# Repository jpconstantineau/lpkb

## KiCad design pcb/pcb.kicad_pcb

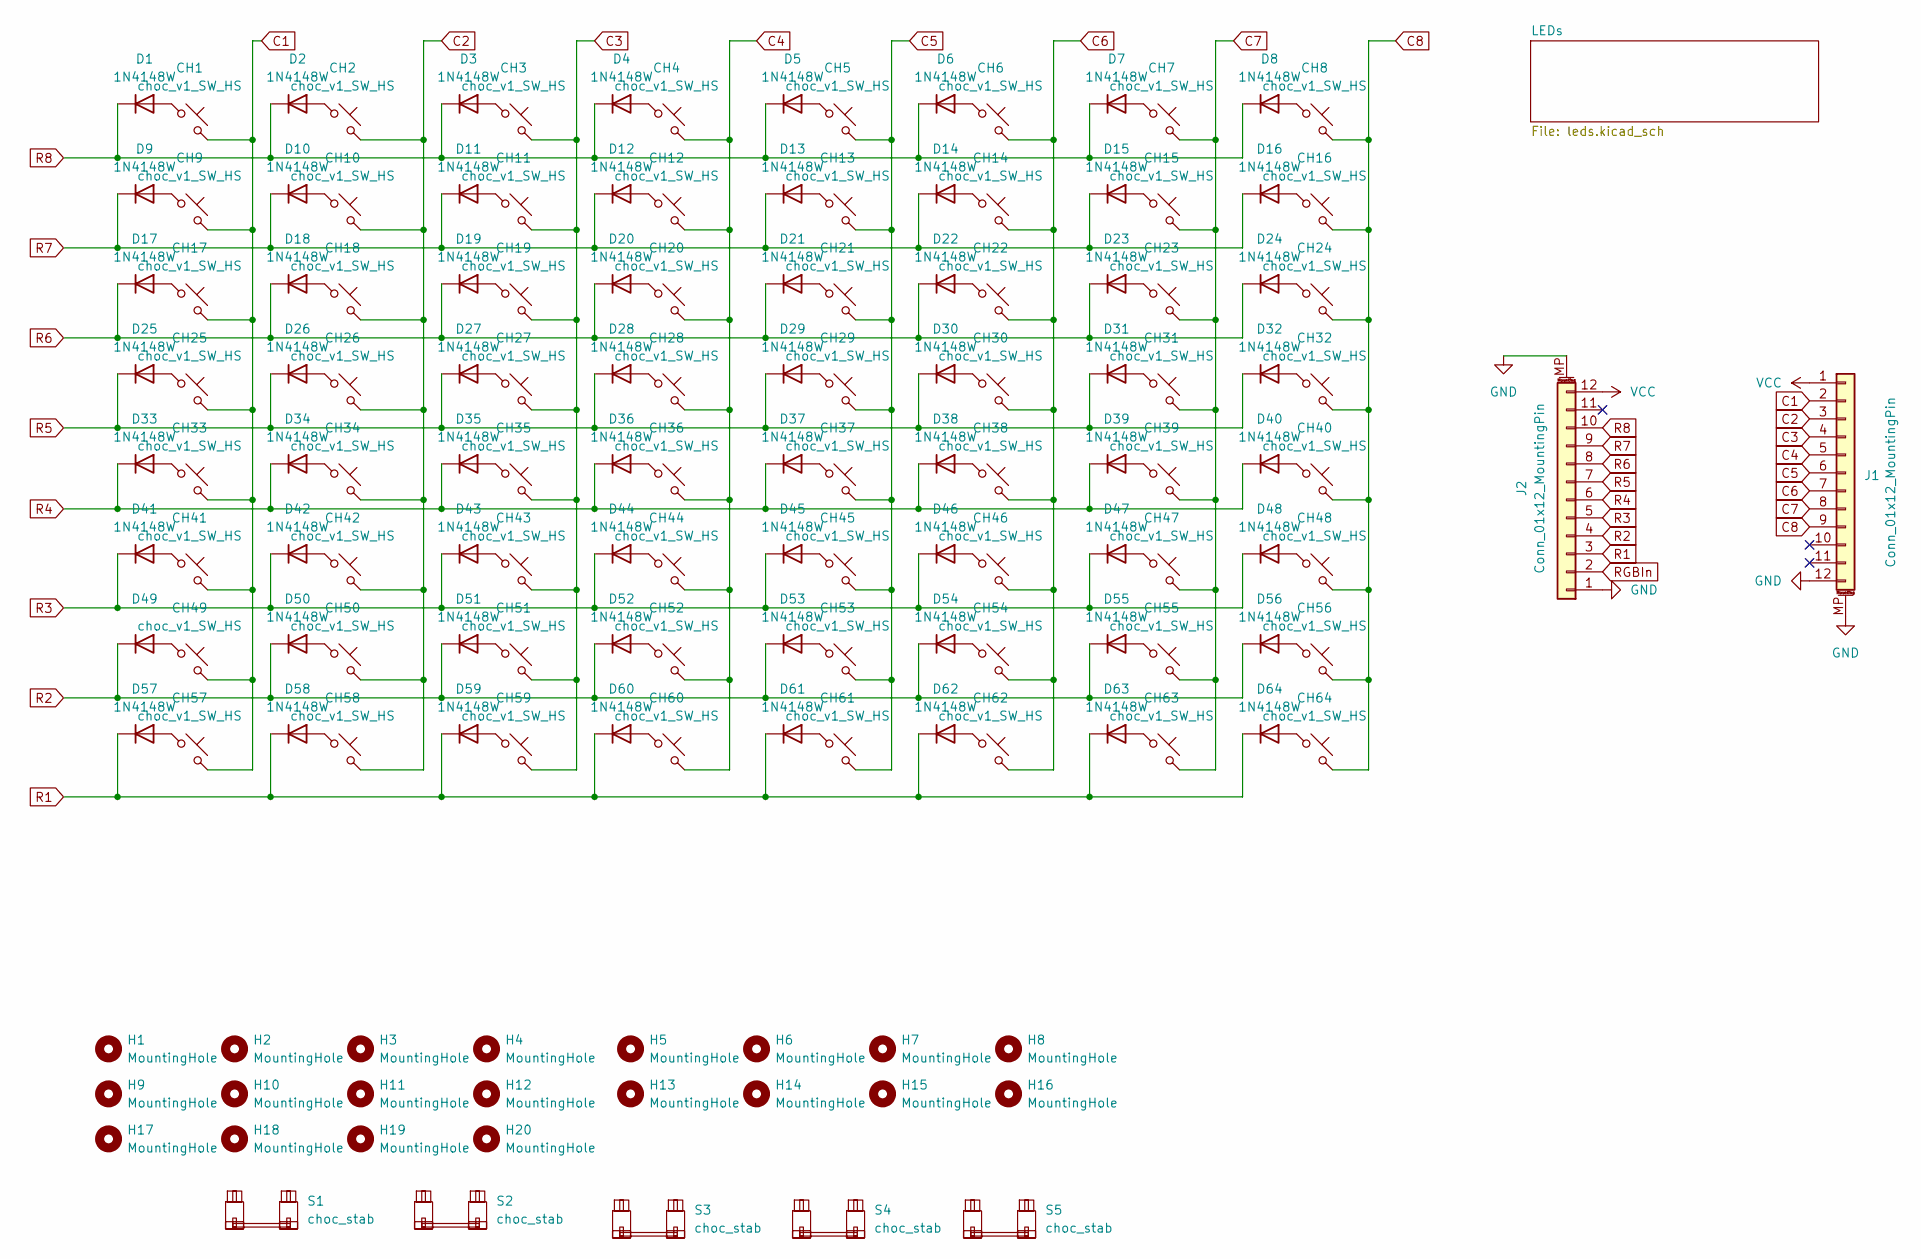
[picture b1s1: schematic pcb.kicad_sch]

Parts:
CH1, CH2, CH3, CH4, CH5, CH6, CH7, CH8, CH9, CH10, CH11, CH12, CH13, CH14, CH15, CH16, CH17, CH18, CH19, CH20, CH21, CH22, CH23, CH24, CH25, CH26, CH27, CH28, CH29, CH30, CH31, CH32, CH33, CH34, CH35, CH36, CH37, CH38, CH39, CH40, CH41, CH42, CH43, CH44, CH45, CH46, CH47, CH48, CH49, CH50, CH51, CH52, CH53, CH54, CH55, CH56, CH57, CH58, CH59, CH60, CH61, CH62, CH63, CH64: choc_v1_SW_HS; SW_choc_v1_HS_CPG135001S30_1u
D1, D2, D3, D4, D5, D6, D7, D8, D9, D10, D11, D12, D13, D14, D15, D16, D17, D18, D19, D20, D21, D22, D23, D24, D25, D26, D27, D28, D29, D30, D31, D32, D33, D34, D35, D36, D37, D38, D39, D40, D41, D42, D43, D44, D45, D46, D47, D48, D49, D50, D51, D52, D53, D54, D55, D56, D57, D58, D59, D60, D61, D62, D63, D64: 1N4148W; D_SOD-123
H1, H2, H3, H4, H5, H6, H7, H8, H9, H10, H11, H12, H13, H14, H15, H16, H17, H18, H19, H20: MountingHole; MountingHole_2.2mm_M2_ISO14580
J1, J2: Conn_01x12_MountingPin; JUSHUO-AFC07-S12FCC-00_C11051_1x12-1MP_P0.50mm_Horizontal
S1, S2, S3, S4, S5: choc_stab; STAB_choc_2u

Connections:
C1: CH1.2, CH9.2, CH17.2, CH25.2, CH33.2, CH41.2, CH49.2, CH57.2, J1.2
C2: CH2.2, CH10.2, CH18.2, CH26.2, CH34.2, CH42.2, CH50.2, CH58.2, J1.3
C3: CH3.2, CH11.2, CH19.2, CH27.2, CH35.2, CH43.2, CH51.2, CH59.2, J1.4
C4: CH4.2, CH12.2, CH20.2, CH28.2, CH36.2, CH44.2, CH52.2, CH60.2, J1.5
C5: CH5.2, CH13.2, CH21.2, CH29.2, CH37.2, CH45.2, CH53.2, CH61.2, J1.6
C6: CH6.2, CH14.2, CH22.2, CH30.2, CH38.2, CH46.2, CH54.2, CH62.2, J1.7
C7: CH7.2, CH15.2, CH23.2, CH31.2, CH39.2, CH47.2, CH55.2, CH63.2, J1.8
C8: CH8.2, CH16.2, CH24.2, CH32.2, CH40.2, CH48.2, CH56.2, CH64.2, J1.9
GND: J1.12, J1.MP (MountPin), J2.1, J2.MP (MountPin); also elsewhere on the board
unnamed: CH1.1, D1.2 (A)
unnamed: CH2.1, D2.2 (A)
unnamed: CH3.1, D3.2 (A)
unnamed: CH4.1, D4.2 (A)
unnamed: CH5.1, D5.2 (A)
unnamed: CH6.1, D6.2 (A)
unnamed: CH7.1, D7.2 (A)
unnamed: CH8.1, D8.2 (A)
unnamed: CH9.1, D9.2 (A)
unnamed: CH10.1, D10.2 (A)
unnamed: CH11.1, D11.2 (A)
unnamed: CH12.1, D12.2 (A)
unnamed: CH13.1, D13.2 (A)
unnamed: CH14.1, D14.2 (A)
unnamed: CH15.1, D15.2 (A)
unnamed: CH16.1, D16.2 (A)
unnamed: CH17.1, D17.2 (A)
unnamed: CH18.1, D18.2 (A)
unnamed: CH19.1, D19.2 (A)
unnamed: CH20.1, D20.2 (A)
unnamed: CH21.1, D21.2 (A)
unnamed: CH22.1, D22.2 (A)
unnamed: CH23.1, D23.2 (A)
unnamed: CH24.1, D24.2 (A)
unnamed: CH25.1, D25.2 (A)
unnamed: CH26.1, D26.2 (A)
unnamed: CH27.1, D27.2 (A)
unnamed: CH28.1, D28.2 (A)
unnamed: CH29.1, D29.2 (A)
unnamed: CH30.1, D30.2 (A)
unnamed: CH31.1, D31.2 (A)
unnamed: CH32.1, D32.2 (A)
unnamed: CH33.1, D33.2 (A)
unnamed: CH34.1, D34.2 (A)
unnamed: CH35.1, D35.2 (A)
unnamed: CH36.1, D36.2 (A)
unnamed: CH37.1, D37.2 (A)
unnamed: CH38.1, D38.2 (A)
unnamed: CH39.1, D39.2 (A)
unnamed: CH40.1, D40.2 (A)
unnamed: CH41.1, D41.2 (A)
unnamed: CH42.1, D42.2 (A)
unnamed: CH43.1, D43.2 (A)
unnamed: CH44.1, D44.2 (A)
unnamed: CH45.1, D45.2 (A)
unnamed: CH46.1, D46.2 (A)
unnamed: CH47.1, D47.2 (A)
unnamed: CH48.1, D48.2 (A)
unnamed: CH49.1, D49.2 (A)
unnamed: CH50.1, D50.2 (A)
unnamed: CH51.1, D51.2 (A)
unnamed: CH52.1, D52.2 (A)
unnamed: CH53.1, D53.2 (A)
unnamed: CH54.1, D54.2 (A)
unnamed: CH55.1, D55.2 (A)
unnamed: CH56.1, D56.2 (A)
unnamed: CH57.1, D57.2 (A)
unnamed: CH58.1, D58.2 (A)
unnamed: CH59.1, D59.2 (A)
unnamed: CH60.1, D60.2 (A)
unnamed: CH61.1, D61.2 (A)
unnamed: CH62.1, D62.2 (A)
unnamed: CH63.1, D63.2 (A)
unnamed: CH64.1, D64.2 (A)
R1: D57.1 (K), D58.1 (K), D59.1 (K), D60.1 (K), D61.1 (K), D62.1 (K), D63.1 (K), D64.1 (K), J2.3
R2: D49.1 (K), D50.1 (K), D51.1 (K), D52.1 (K), D53.1 (K), D54.1 (K), D55.1 (K), D56.1 (K), J2.4
R3: D41.1 (K), D42.1 (K), D43.1 (K), D44.1 (K), D45.1 (K), D46.1 (K), D47.1 (K), D48.1 (K), J2.5
R4: D33.1 (K), D34.1 (K), D35.1 (K), D36.1 (K), D37.1 (K), D38.1 (K), D39.1 (K), D40.1 (K), J2.6
R5: D25.1 (K), D26.1 (K), D27.1 (K), D28.1 (K), D29.1 (K), D30.1 (K), D31.1 (K), D32.1 (K), J2.7
R6: D17.1 (K), D18.1 (K), D19.1 (K), D20.1 (K), D21.1 (K), D22.1 (K), D23.1 (K), D24.1 (K), J2.8
R7: D9.1 (K), D10.1 (K), D11.1 (K), D12.1 (K), D13.1 (K), D14.1 (K), D15.1 (K), D16.1 (K), J2.9
R8: D1.1 (K), D2.1 (K), D3.1 (K), D4.1 (K), D5.1 (K), D6.1 (K), D7.1 (K), D8.1 (K), J2.10
RGBIn: J2.2; also elsewhere on the board
VCC: J1.1, J2.12; also elsewhere on the board

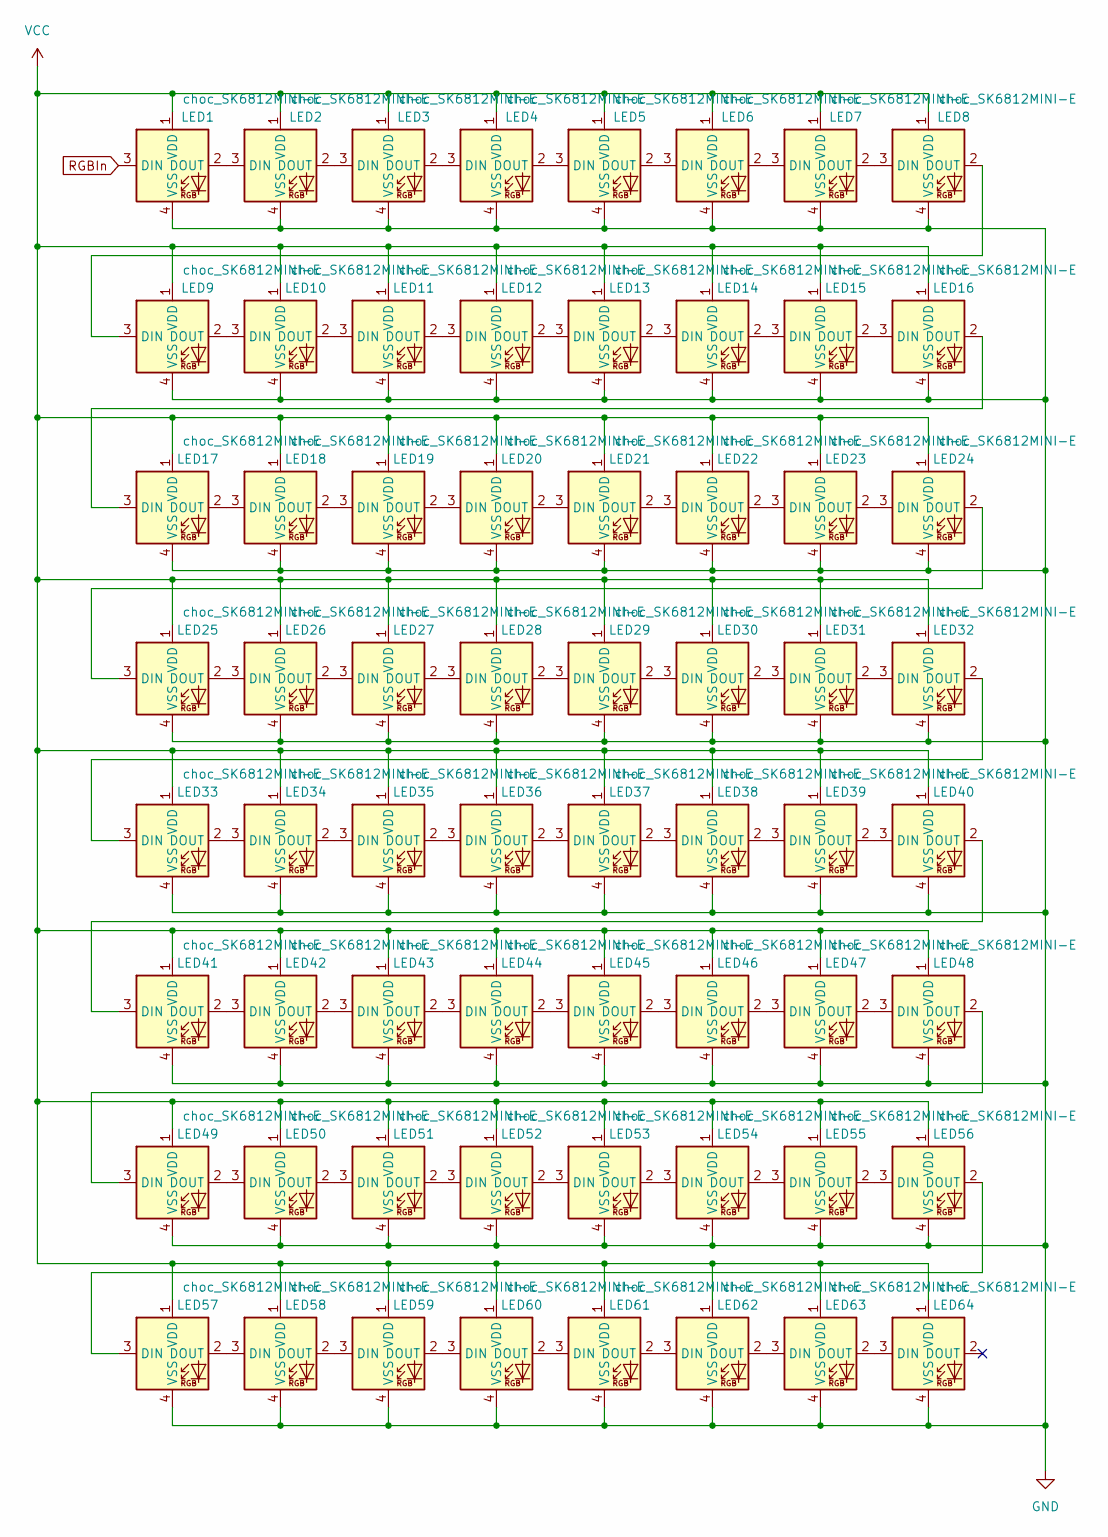
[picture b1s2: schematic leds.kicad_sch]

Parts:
LED1, LED2, LED3, LED4, LED5, LED6, LED7, LED8, LED9, LED10, LED11, LED12, LED13, LED14, LED15, LED16, LED17, LED18, LED19, LED20, LED21, LED22, LED23, LED24, LED25, LED26, LED27, LED28, LED29, LED30, LED31, LED32, LED33, LED34, LED35, LED36, LED37, LED38, LED39, LED40, LED41, LED42, LED43, LED44, LED45, LED46, LED47, LED48, LED49, LED50, LED51, LED52, LED53, LED54, LED55, LED56, LED57, LED58, LED59, LED60, LED61, LED62, LED63, LED64: choc_SK6812MINI-E; LED_choc_6028R

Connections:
GND: LED1.4 (VSS), LED2.4 (VSS), LED3.4 (VSS), LED4.4 (VSS), LED5.4 (VSS), LED6.4 (VSS), LED7.4 (VSS), LED8.4 (VSS), LED9.4 (VSS), LED10.4 (VSS), LED11.4 (VSS), LED12.4 (VSS), LED13.4 (VSS), LED14.4 (VSS), LED15.4 (VSS), LED16.4 (VSS), LED17.4 (VSS), LED18.4 (VSS), LED19.4 (VSS), LED20.4 (VSS), LED21.4 (VSS), LED22.4 (VSS), LED23.4 (VSS), LED24.4 (VSS), LED25.4 (VSS), LED26.4 (VSS), LED27.4 (VSS), LED28.4 (VSS), LED29.4 (VSS), LED30.4 (VSS), LED31.4 (VSS), LED32.4 (VSS), LED33.4 (VSS), LED34.4 (VSS), LED35.4 (VSS), LED36.4 (VSS), LED37.4 (VSS), LED38.4 (VSS), LED39.4 (VSS), LED40.4 (VSS), LED41.4 (VSS), LED42.4 (VSS), LED43.4 (VSS), LED44.4 (VSS), LED45.4 (VSS), LED46.4 (VSS), LED47.4 (VSS), LED48.4 (VSS), LED49.4 (VSS), LED50.4 (VSS), LED51.4 (VSS), LED52.4 (VSS), LED53.4 (VSS), LED54.4 (VSS), LED55.4 (VSS), LED56.4 (VSS), LED57.4 (VSS), LED58.4 (VSS), LED59.4 (VSS), LED60.4 (VSS), LED61.4 (VSS), LED62.4 (VSS), LED63.4 (VSS), LED64.4 (VSS); also elsewhere on the board
unnamed: LED1.2 (DOUT), LED2.3 (DIN)
unnamed: LED2.2 (DOUT), LED3.3 (DIN)
unnamed: LED3.2 (DOUT), LED4.3 (DIN)
unnamed: LED4.2 (DOUT), LED5.3 (DIN)
unnamed: LED5.2 (DOUT), LED6.3 (DIN)
unnamed: LED6.2 (DOUT), LED7.3 (DIN)
unnamed: LED7.2 (DOUT), LED8.3 (DIN)
unnamed: LED8.2 (DOUT), LED9.3 (DIN)
unnamed: LED9.2 (DOUT), LED10.3 (DIN)
unnamed: LED10.2 (DOUT), LED11.3 (DIN)
unnamed: LED11.2 (DOUT), LED12.3 (DIN)
unnamed: LED12.2 (DOUT), LED13.3 (DIN)
unnamed: LED13.2 (DOUT), LED14.3 (DIN)
unnamed: LED14.2 (DOUT), LED15.3 (DIN)
unnamed: LED15.2 (DOUT), LED16.3 (DIN)
unnamed: LED16.2 (DOUT), LED17.3 (DIN)
unnamed: LED17.2 (DOUT), LED18.3 (DIN)
unnamed: LED18.2 (DOUT), LED19.3 (DIN)
unnamed: LED19.2 (DOUT), LED20.3 (DIN)
unnamed: LED20.2 (DOUT), LED21.3 (DIN)
unnamed: LED21.2 (DOUT), LED22.3 (DIN)
unnamed: LED22.2 (DOUT), LED23.3 (DIN)
unnamed: LED23.2 (DOUT), LED24.3 (DIN)
unnamed: LED24.2 (DOUT), LED25.3 (DIN)
unnamed: LED25.2 (DOUT), LED26.3 (DIN)
unnamed: LED26.2 (DOUT), LED27.3 (DIN)
unnamed: LED27.2 (DOUT), LED28.3 (DIN)
unnamed: LED28.2 (DOUT), LED29.3 (DIN)
unnamed: LED29.2 (DOUT), LED30.3 (DIN)
unnamed: LED30.2 (DOUT), LED31.3 (DIN)
unnamed: LED31.2 (DOUT), LED32.3 (DIN)
unnamed: LED32.2 (DOUT), LED33.3 (DIN)
unnamed: LED33.2 (DOUT), LED34.3 (DIN)
unnamed: LED34.2 (DOUT), LED35.3 (DIN)
unnamed: LED35.2 (DOUT), LED36.3 (DIN)
unnamed: LED36.2 (DOUT), LED37.3 (DIN)
unnamed: LED37.2 (DOUT), LED38.3 (DIN)
unnamed: LED38.2 (DOUT), LED39.3 (DIN)
unnamed: LED39.2 (DOUT), LED40.3 (DIN)
unnamed: LED40.2 (DOUT), LED41.3 (DIN)
unnamed: LED41.2 (DOUT), LED42.3 (DIN)
unnamed: LED42.2 (DOUT), LED43.3 (DIN)
unnamed: LED43.2 (DOUT), LED44.3 (DIN)
unnamed: LED44.2 (DOUT), LED45.3 (DIN)
unnamed: LED45.2 (DOUT), LED46.3 (DIN)
unnamed: LED46.2 (DOUT), LED47.3 (DIN)
unnamed: LED47.2 (DOUT), LED48.3 (DIN)
unnamed: LED48.2 (DOUT), LED49.3 (DIN)
unnamed: LED49.2 (DOUT), LED50.3 (DIN)
unnamed: LED50.2 (DOUT), LED51.3 (DIN)
unnamed: LED51.2 (DOUT), LED52.3 (DIN)
unnamed: LED52.2 (DOUT), LED53.3 (DIN)
unnamed: LED53.2 (DOUT), LED54.3 (DIN)
unnamed: LED54.2 (DOUT), LED55.3 (DIN)
unnamed: LED55.2 (DOUT), LED56.3 (DIN)
unnamed: LED56.2 (DOUT), LED57.3 (DIN)
unnamed: LED57.2 (DOUT), LED58.3 (DIN)
unnamed: LED58.2 (DOUT), LED59.3 (DIN)
unnamed: LED59.2 (DOUT), LED60.3 (DIN)
unnamed: LED60.2 (DOUT), LED61.3 (DIN)
unnamed: LED61.2 (DOUT), LED62.3 (DIN)
unnamed: LED62.2 (DOUT), LED63.3 (DIN)
unnamed: LED63.2 (DOUT), LED64.3 (DIN)
RGBIn: LED1.3 (DIN); also elsewhere on the board
VCC: LED1.1 (VDD), LED2.1 (VDD), LED3.1 (VDD), LED4.1 (VDD), LED5.1 (VDD), LED6.1 (VDD), LED7.1 (VDD), LED8.1 (VDD), LED9.1 (VDD), LED10.1 (VDD), LED11.1 (VDD), LED12.1 (VDD), LED13.1 (VDD), LED14.1 (VDD), LED15.1 (VDD), LED16.1 (VDD), LED17.1 (VDD), LED18.1 (VDD), LED19.1 (VDD), LED20.1 (VDD), LED21.1 (VDD), LED22.1 (VDD), LED23.1 (VDD), LED24.1 (VDD), LED25.1 (VDD), LED26.1 (VDD), LED27.1 (VDD), LED28.1 (VDD), LED29.1 (VDD), LED30.1 (VDD), LED31.1 (VDD), LED32.1 (VDD), LED33.1 (VDD), LED34.1 (VDD), LED35.1 (VDD), LED36.1 (VDD), LED37.1 (VDD), LED38.1 (VDD), LED39.1 (VDD), LED40.1 (VDD), LED41.1 (VDD), LED42.1 (VDD), LED43.1 (VDD), LED44.1 (VDD), LED45.1 (VDD), LED46.1 (VDD), LED47.1 (VDD), LED48.1 (VDD), LED49.1 (VDD), LED50.1 (VDD), LED51.1 (VDD), LED52.1 (VDD), LED53.1 (VDD), LED54.1 (VDD), LED55.1 (VDD), LED56.1 (VDD), LED57.1 (VDD), LED58.1 (VDD), LED59.1 (VDD), LED60.1 (VDD), LED61.1 (VDD), LED62.1 (VDD), LED63.1 (VDD), LED64.1 (VDD); also elsewhere on the board

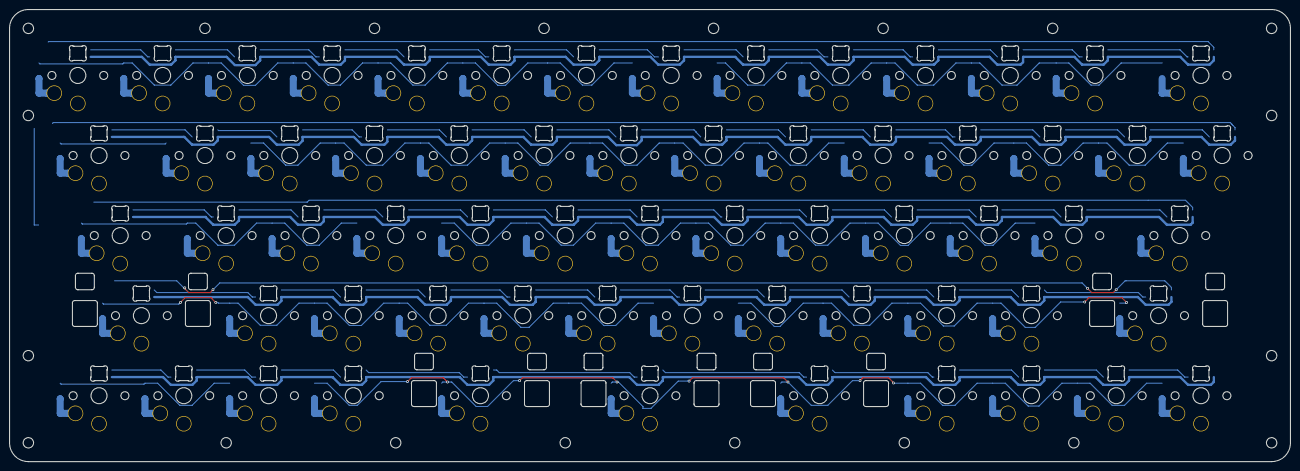
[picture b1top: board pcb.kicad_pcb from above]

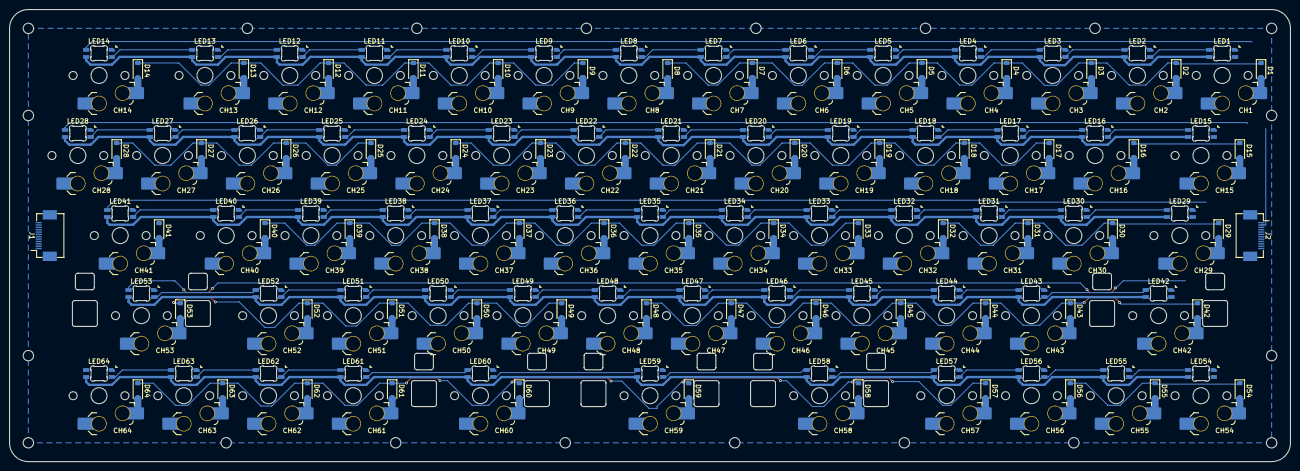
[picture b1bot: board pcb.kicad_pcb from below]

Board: 2 copper layers, 271.9 x 95.9 mm, 219 parts (194 on the bottom side), 146 nets.

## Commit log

2024-11-20 added schematic
2024-11-20 added PCB placement and size
2024-11-21 initial routing start
2024-11-22 horizontal routing
2024-11-22 routed - still need to check screw clearance
